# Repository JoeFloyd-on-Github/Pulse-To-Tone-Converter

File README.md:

# Pulse-to-Tone Converter (ATtiny85)

An internal **pulse-to-tone converter**. It sits inside a classic rotary
telephone and turns the dial's pulses (loop interruptions) into **DTMF
tones**, so the phone works on a modern tone-only line or VoIP adapter. It is
built around an **ATtiny85** on a small PCB, **BRD170127**.

> **Origin and credit.** The design comes from the open-source
> **[Pulse to Tone Converter](https://hackaday.io/project/28557-pulse-to-tone-converter)**
> by **LieBtrau** (Christoph Tack) on Hackaday.io and
> [GitHub](https://github.com/LieBtrau/pulse-dtmf-converter). This repository
> documents the kit built from it (rev R2), analyses it, and adds a
> redesigned board (rev V3).

## Board revisions

Each revision has its own parts list, firmware and build instructions. Use
the folder for the board you have.

| | **Rev R2**: the original kit board | **Rev V3**: the redesign |
|---|---|---|
| Folder | [`hardware_r2/`](hardware_r2/README.md) | [`hardware_v3/`](hardware_v3/README.md) |
| Board | LieBtrau's BRD170127/2 (EasyEDA): Gerbers, schematic, BOM, photos | KiCad 9, routed and DRC-clean, in the same outline with the jacks in the same places ([`hardware_v3/kicad`](hardware_v3/kicad/README.md)) |
| What's different | — | runs on loop currents down to about 1.5 mA (R2 needs about 6.5 mA); a PNP helper on each shunt regulator; no op-amp; optional CR1632 backup |
| Firmware source | upstream commit **`31ae4ba` (2019-07-06)**, Arduino IDE era ([`hardware_r2/firmware`](hardware_r2/firmware/README.md)) | upstream **`593e746` (2023)** plus V3 battery control ([`hardware_v3/firmware`](hardware_v3/firmware/README.md)) |
| Firmware image | `hardware_r2/firmware/images/ATTINY85V@SOIC8.hex` (production) | `hardware_v3/firmware/images/pulse-dtmf-converter-v3.hex` |
| Send delay after the last digit | 3 s | 1.2 s (configurable) |
| PB2 (ATtiny pin 7) | "mode" input, never wired on the board | coin-cell enable (BATT_EN) |
| Toolchain | Arduino IDE 1.8.13 + ATTinyCore 1.4.1 + Bounce2 2.55 | Arduino IDE 2 or arduino-cli + ATTinyCore 1.5.2 + Bounce2 2.71 |
| Fuses | L 0xFF, H 0xD5 (BOD 2.7 V), E 0xFF | the same |
| Programming | Arduino Uno as ISP, chip in a SOIC-8 ZIF adapter; or an XGecu programmer | the same Uno setup, in circuit with a SOIC-8 clip; or an XGecu programmer |
| Build docs | the toolchain guide + `KIT_build.doc` | [`hardware_v3/firmware/README.md`](hardware_v3/firmware/README.md) §3–5 + the KiCad fab files |
| Status | built and sold as a kit | designed and simulated; **not built yet** |

### About the firmware versions

Upstream's code changed after the R2 kits were made. The repo used to carry
upstream's **2023** source as if it were the kit firmware. It is not: the R2
production image was rebuilt from the **2019** source and matches it in size,
constants and RAM layout. The 2023 update moved the project from the Arduino
IDE to **PlatformIO**, shortened the send delay from 3 s to 1.2 s, and bounded
the digit buffer. The details are in
[`hardware_r2/firmware/README.md`](hardware_r2/firmware/README.md) §1 and §4.

## Also in this repo

| Path | Contents |
|---|---|
| [`ANALYSIS.md`](ANALYSIS.md) | engineering analysis of the original board and firmware: power, regulators, pulse decoding, DTMF generation, features |
| [`hardware_v3/spice`](hardware_v3/spice/README.md) | ngspice comparison of R2 and V3 |
| `third_party/` | **ATTinyCore** ([Spence Konde](https://github.com/SpenceKonde/ATTinyCore); a 1.4.2-dev snapshot; see its `LICENSE.md`) and **Bounce2** 2.55 ([Thomas Fredericks](https://github.com/thomasfredericks/Bounce2), MIT), as bundled with the R2 kit build |
| `WEB_SAVES/` | local copies of the upstream web pages and the ETSI DTMF specification, in case the sites go offline |

## License

- **Firmware:** both `hardware_r2/firmware` (upstream, verbatim) and
  `hardware_v3/firmware` (upstream plus the V3 changes) are **GPL v3**,
  © 2018 Christoph Tack. See the `LICENSE` file in each folder.
- **Bundled libraries** (ATTinyCore, Bounce2) keep their own licenses.
- The **documentation** (`ANALYSIS.md`, the READMEs, the SPICE and KiCad work)
  is this project's own. The boards derive from the upstream design; check the
  upstream project before redistributing hardware.

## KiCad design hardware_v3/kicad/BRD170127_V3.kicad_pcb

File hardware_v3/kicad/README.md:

# BRD170127 rev V3: KiCad design and manufacturing files

This is a routed, DRC-clean, 2-layer board in the rev-R2 outline (49 × 34 mm).
The three RJ11 jacks are in the same places as on R2, so V3 is a drop-in
replacement. The circuit is the one simulated in [`../spice`](../spice).

**Open in KiCad 9:** `BRD170127_V3.kicad_pro`. The project-local libraries are
`BRD170127.pretty` (the RJ11 footprint copied from the R2 board, and the
cell-lead pads) and `BRD170127.kicad_sym` (TLV431 with the onsemi SOT-23 pinout).

## Status

| Check | Result |
|---|---|
| DRC (`kicad-cli pcb drc --severity-all`) | **0 violations, 0 unconnected** |
| Schematic parity | **0 issues** |
| ERC | no electrical errors. The only warnings are that kicad-cli has no global symbol-library table on this machine; the symbols are embedded in the schematic. |
| R2 hole compatibility | all 18 jack pins and 6 locating posts match the R2 drill file to within 0.02 mm. C1 sits 0.3 mm higher, to clear the rotary jack's body. |

## Ordering (`fab/`)

| File | Use |
|---|---|
| `BRD170127_V3_gerbers.zip` | upload to the PCB fab: 2 layers, 1.6 mm, HASL or ENIG, any colour |
| `BRD170127_V3_bom_jlc.csv`, `BRD170127_V3_cpl_jlc.csv` | JLCPCB-style assembly files for the 41 top-side SMD parts |
| `BRD170127_V3_bom.csv` | the full BOM, including the hand-soldered parts |
| `BRD170127_V3_schematic.pdf` | the schematic |
| `BRD170127_V3_assembly.pdf` | every reference designator. 14 labels did not fit on the silkscreen of this dense board and appear only here. |
| `render_top.png`, `render_bottom.png` | 3-D renders |

Design rules: tracks at least 0.2 mm (0.5 mm on the line, VCC, VEE and GND
nets), clearance 0.2 mm, vias 0.6/0.3 mm (0.8/0.4 mm on line nets), GND pour
on both layers. Any standard 2-layer service can make it.

**Before you order:**
- **Fill in the LCSC numbers.** They are known for the parts reused from R2:
  BAT46WH C127989, TLV431A C56765, BC856B C181144, ATtiny85V C152192 and the
  8 MHz crystal C108703. The 0805 passives, BCX53-16 (Q2/Q4) and DMG2301L (Q3)
  have only an MPN or value. Pick stock parts at order time.
- In the fab's assembly preview, check the rotation of the SOT-23/SOT-89/SOIC
  parts. KiCad and JLCPCB sometimes disagree on the zero orientation.
- **Hand-soldered parts:** the three RJ11 jacks (mounted as on R2), the
  470 µF / 6.3 V radial C1 (8 mm diameter, 3.5 mm pitch), and the CR1632 holder
  on flying leads to the BT1 pads (+ is the square pad).

## Circuit changes from the original (rev R2)

| Area | Original | V3 | Why |
|---|---|---|---|
| Upper shunt | TLV431 alone, 4.59 V, plus a 1k bleeder | TLV431 U2 + BCX53 Q2 (R15 470, R16 220, C12 1n), 5.0 V (R1 100k / R6 33k), 22k bleeder R17 | each TLV431 only biases its PNP; R17 still pulls VCC down quickly so pulse breaks are detected |
| Lower shunt / line modulator | TLV431 U3 carries the whole loop current | U3 + BCX53 Q4 (R19 470, R20 220), R5 47k | the original runs U3 at 25–40 mA against a 15 mA rating |
| DTMF filter | MCP6022: 4th-order active filter + V-to-I | passive 2-pole RC (R12/R13/C8, R10/C9) into Q1 (R2 39k emitter resistor) | removes 2 mA of standing current |
| Reservoir | 470 µF behind D5 | same | the simulation shows it rides through dialing down to about 1.5 mA of loop current |
| Coin cell | none | CR1632 → Q3 (DMG2301L) → D6 → VDD; gate pull-up R18 1M; BATT_EN = **PB2 (pin 7)** | kept at the owner's request; the simulation shows it is rarely needed |
| Test points | none | TP1 VCC, TP2 VDD, TP3 BATT+, TP4 BATT_EN, TP5 CELL, TP6 GND | for bench verification (see `../spice/README.md`) |
| Passive parts | 1206 | 0805 | the extra parts have to fit the same area |

**Firmware:** BATT_EN is on **PB2**, the only free pin: PB1 is the DTMF PWM
output (OC1A), and the crystal uses PB3/PB4. The V3 firmware, its tools and
fuses, and the in-circuit programming (Arduino as ISP with a SOIC-8 clip on U1)
are in [`../firmware`](../firmware/README.md).

## Regenerating

Everything is built from `design.py`, which defines the parts, nets and
placement:

```sh
python3 gen_sch.py          # schematic (net-label style; symbols flattened and embedded)
python3 gen_pcb.py          # placed, unrouted board + project/library tables
python3 route.py            # import route/board.ses, widen neck-downs, refill pours, place labels
python3 make_fab.py         # DRC + parity + ERC, then everything in fab/
```

To route from scratch instead of reusing `route/board.ses`:

```sh
FREEROUTING_JAR=/path/to/freerouting-2.5.0.jar python3 route.py --autoroute
```

Freerouting is run headless with analytics disabled and Java's network access
pointed at a dead proxy.

If you edit the board by hand in KiCad, stop using the generators: they
overwrite the `.kicad_pcb` and `.kicad_sch` files.

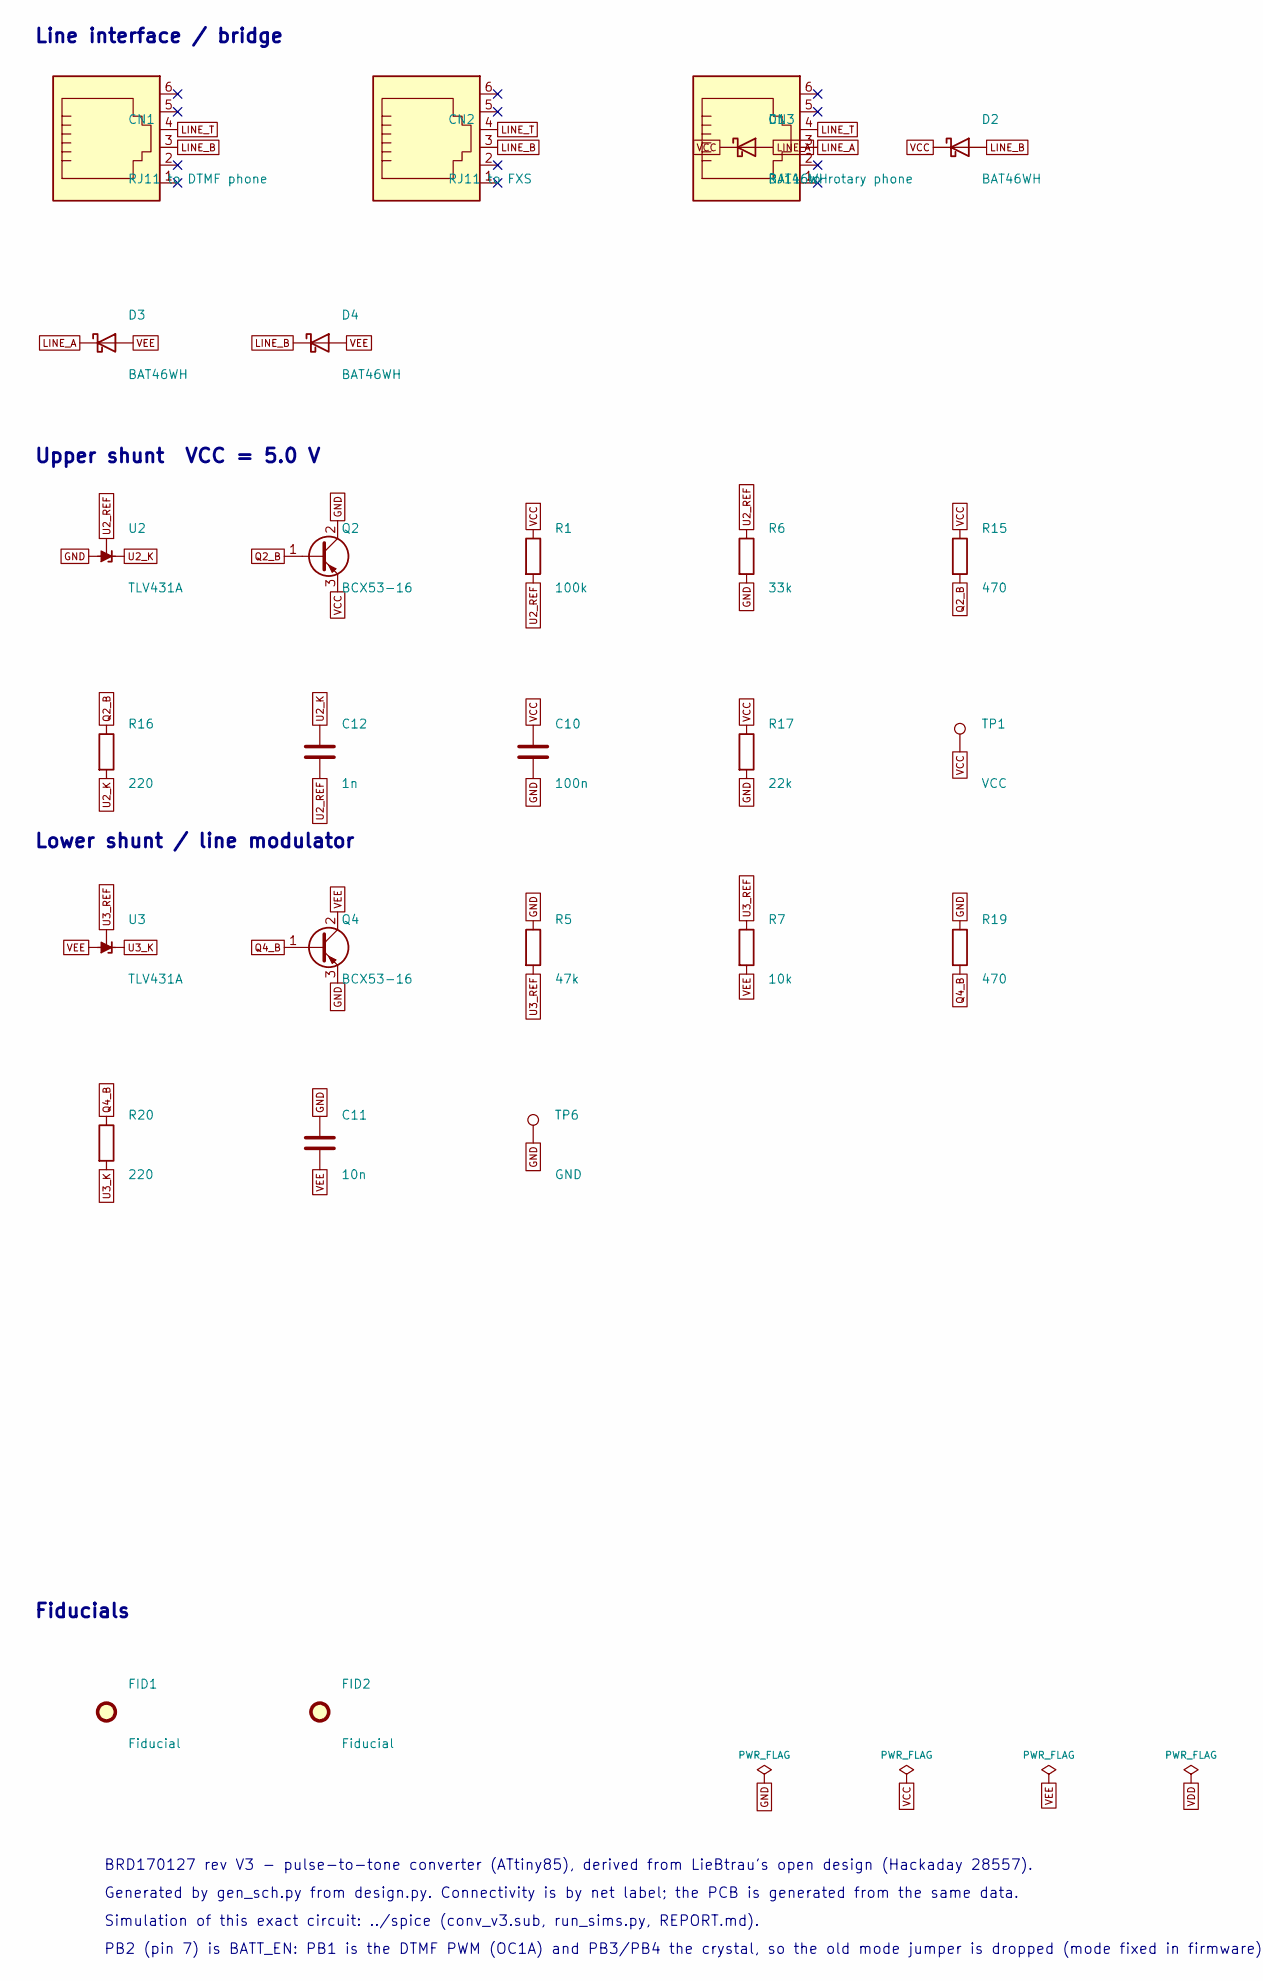
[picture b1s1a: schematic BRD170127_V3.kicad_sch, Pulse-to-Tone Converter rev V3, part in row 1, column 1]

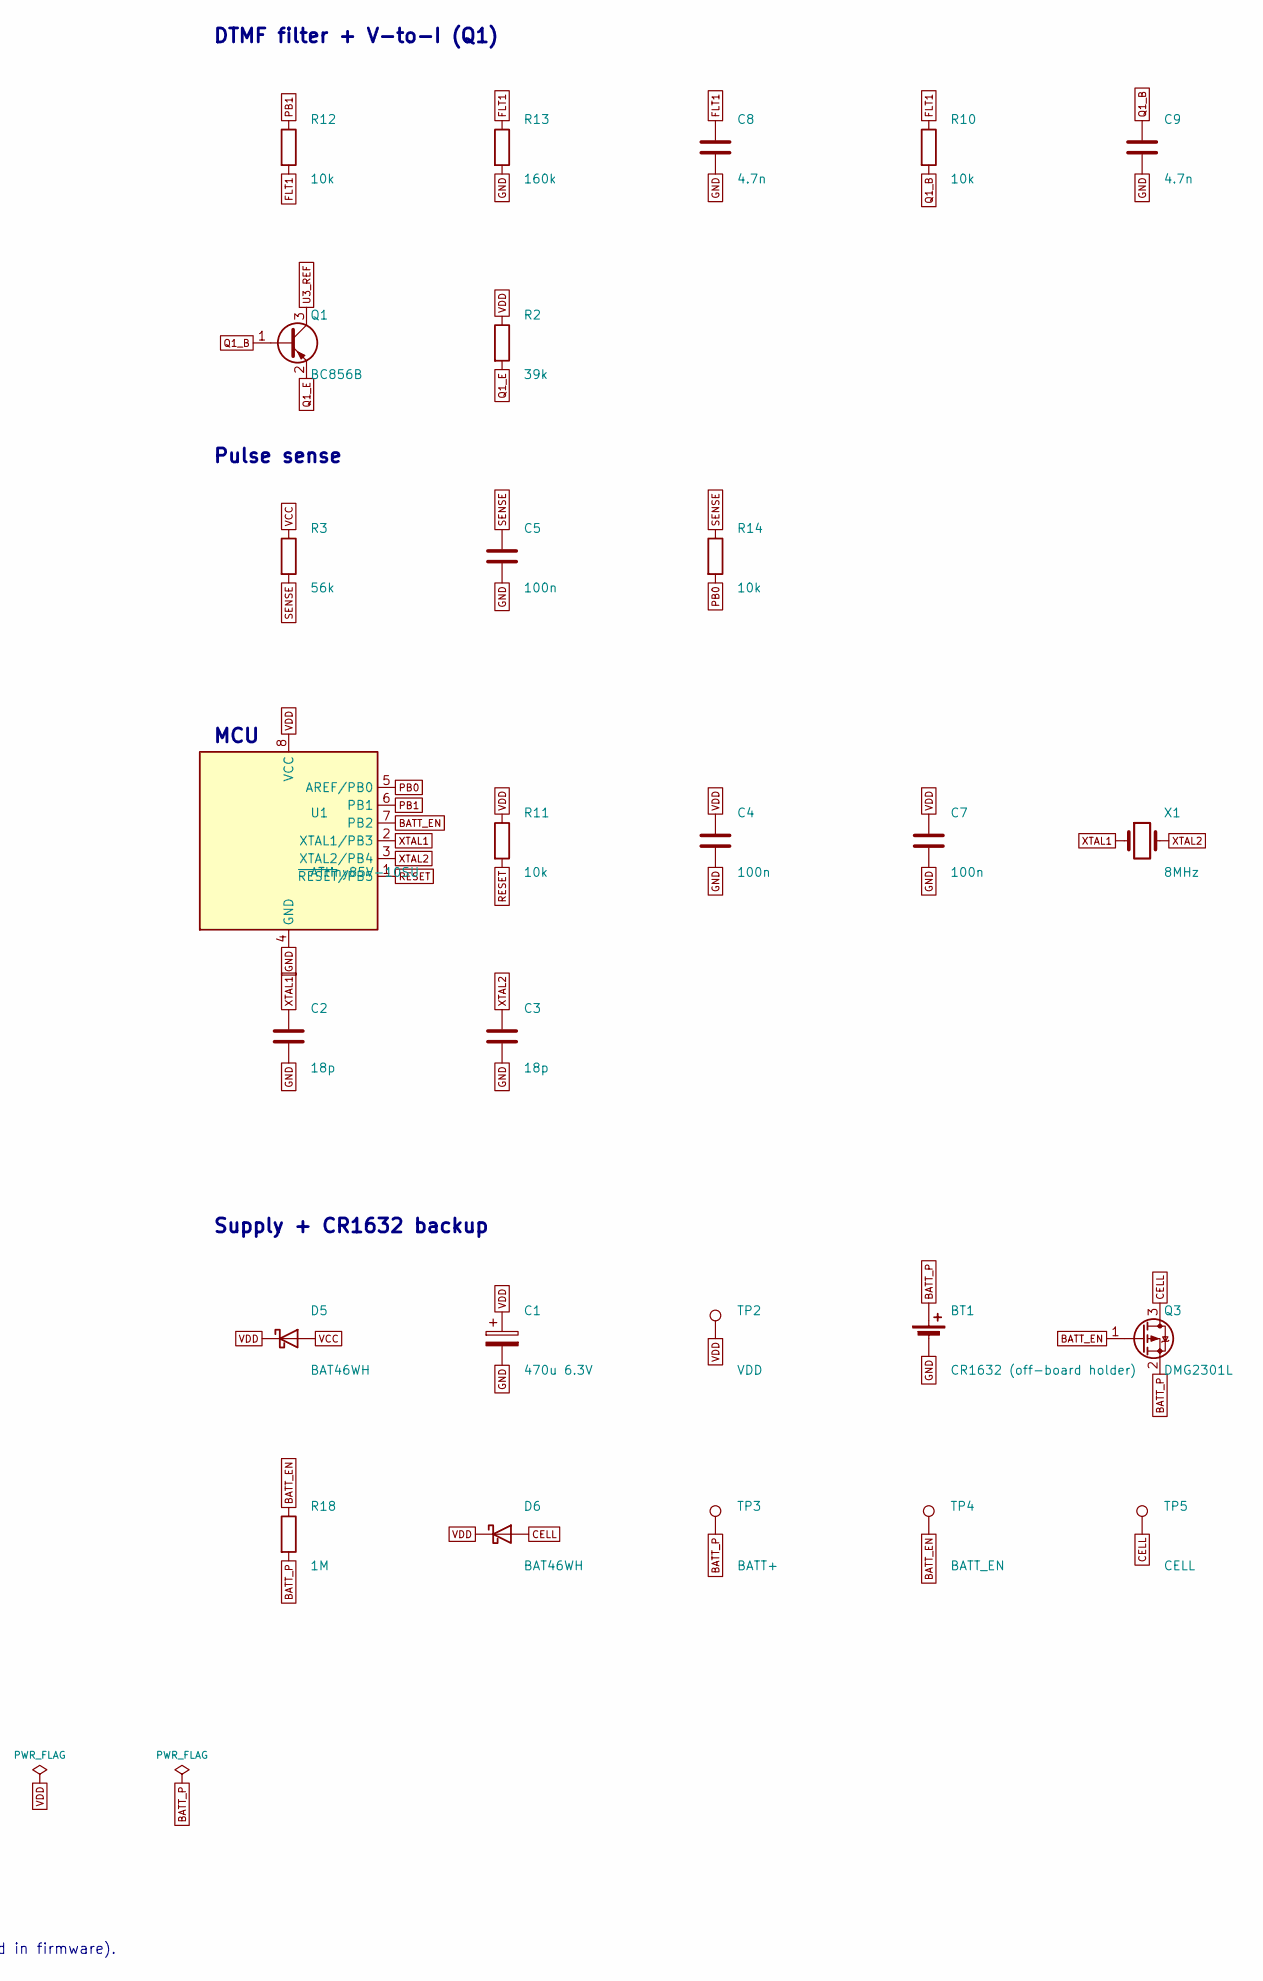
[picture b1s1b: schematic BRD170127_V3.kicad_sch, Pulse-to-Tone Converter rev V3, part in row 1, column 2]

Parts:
BT1: CR1632 (off-board holder); CELL_LEADS_2PAD; MPN CR1632 + wire-lead holder
C1: 470u 6.3V; CP_Radial_D8.0mm_P3.50mm; MPN 470uF 6.3V radial 8 mm, 3.5 mm pitch
C2, C3: 18p; C_0805_2012Metric
C4, C5, C7, C10: 100n; C_0805_2012Metric
C8, C9: 4.7n; C_0805_2012Metric
C11: 10n; C_0805_2012Metric
C12: 1n; C_0805_2012Metric
CN1: RJ11 to DTMF phone; RJ11_6P6C_BRD170127; MPN 6P6C side-entry, as rev R2
CN2: RJ11 to FXS; RJ11_6P6C_BRD170127; MPN 6P6C side-entry, as rev R2
CN3: RJ11 to rotary phone; RJ11_6P6C_BRD170127; MPN 6P6C side-entry, as rev R2
D1, D2, D3, D4, D5, D6: BAT46WH; D_SOD-123; MPN BAT46WH; LCSC C127989
FID1, FID2: Fiducial; Fiducial_1mm_Mask2mm
Q1: BC856B; SOT-23; MPN BC856B; LCSC C181144
Q2, Q4: BCX53-16; SOT-89-3; MPN BCX53-16
Q3: DMG2301L; SOT-23; MPN DMG2301L-7
R1: 100k; R_0805_2012Metric
R2: 39k; R_0805_2012Metric
R3: 56k; R_0805_2012Metric
R5: 47k; R_0805_2012Metric
R6: 33k; R_0805_2012Metric
R7, R10, R11, R12, R14: 10k; R_0805_2012Metric
R13: 160k; R_0805_2012Metric
R15, R19: 470; R_0805_2012Metric
R16, R20: 220; R_0805_2012Metric
R17: 22k; R_0805_2012Metric
R18: 1M; R_0805_2012Metric
TP1: VCC; TestPoint_Pad_D1.5mm
TP2: VDD; TestPoint_Pad_D1.5mm
TP3: BATT+; TestPoint_Pad_D1.5mm
TP4: BATT_EN; TestPoint_Pad_D1.5mm
TP5: CELL; TestPoint_Pad_D1.5mm
TP6: GND; TestPoint_Pad_D1.5mm
U1: ATtiny85V-10SU; SOIC-8_5.3x5.3mm_P1.27mm; MPN ATTINY85V-10SU; LCSC C152192
U2, U3: TLV431A; SOT-23; MPN TLV431ASN1T1G; LCSC C56765
X1: 8MHz; Crystal_SMD_HC49-SD; MPN HC-49/US SMD 8.000 MHz 18 pF; LCSC C108703

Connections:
BATT_EN: Q3.1 (G), R18.1, TP4.1, U1.7 (PB2)
BATT_P: BT1.1 (+), Q3.2 (S), R18.2, TP3.1
CELL: D6.2 (A), Q3.3 (D), TP5.1
FLT1: C8.1, R10.1, R12.2, R13.1
GND: BT1.2 (-), C1.2, C2.2, C3.2, C4.2, C5.2, C7.2, C8.2, C9.2, C10.2, C11.1, Q2.2 (C), Q4.3 (E), R5.1, R6.2, R13.2, R17.2, R19.1, TP6.1, U1.4 (GND), U2.3 (A)
LINE_A: CN3.3, D1.2 (A), D3.1 (K)
LINE_B: CN1.3, CN2.3, D2.2 (A), D4.1 (K)
LINE_T: CN1.4, CN2.4, CN3.4
PB0: R14.2, U1.5 (AREF/PB0)
PB1: R12.1, U1.6 (PB1)
Q1_B: C9.1, Q1.1 (B), R10.2
Q1_E: Q1.2 (E), R2.2
Q2_B: Q2.1 (B), R15.2, R16.1
Q4_B: Q4.1 (B), R19.2, R20.1
RESET: R11.2, U1.1 (~RESET/PB5)
SENSE: C5.1, R3.2, R14.1
U2_K: C12.1, R16.2, U2.2 (K)
U2_REF: C12.2, R1.2, R6.1, U2.1 (REF)
U3_K: R20.2, U3.2 (K)
U3_REF: Q1.3 (C), R5.2, R7.1, U3.1 (REF)
VCC: C10.1, D1.1 (K), D2.1 (K), D5.2 (A), Q2.3 (E), R1.1, R3.1, R15.1, R17.1, TP1.1
VDD: C1.1, C4.1, C7.1, D5.1 (K), D6.1 (K), R2.1, R11.1, TP2.1, U1.8 (VCC)
VEE: C11.2, D3.2 (A), D4.2 (A), Q4.2 (C), R7.2, U3.3 (A)
XTAL1: C2.1, U1.2 (XTAL1/PB3), X1.1
XTAL2: C3.1, U1.3 (XTAL2/PB4), X1.2

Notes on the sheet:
Line interface / bridge
Upper shunt VCC = 5.0 V
Lower shunt / line modulator
DTMF filter + V-to-I (Q1)
Pulse sense
MCU
Supply + CR1632 backup
Fiducials
BRD170127 rev V3 - pulse-to-tone converter (ATtiny85), derived from LieBtrau's open design (Hackaday 28557).
Generated by gen_sch.py from design.py. Connectivity is by net label; the PCB is generated from the same data.
Simulation of this exact circuit: ../spice (conv_v3.sub, run_sims.py, REPORT.md).
PB2 (pin 7) is BATT_EN: PB1 is the DTMF PWM (OC1A) and PB3/PB4 the crystal, so the old mode jumper is dropped (mode fixed in firmware).

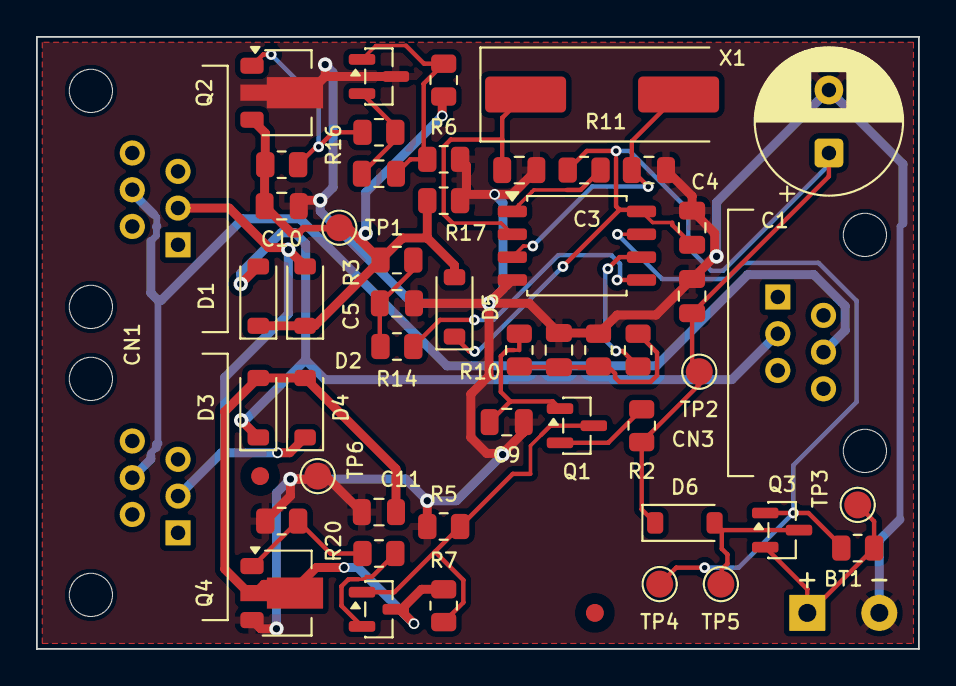
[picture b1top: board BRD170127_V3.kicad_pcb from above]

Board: 2 copper layers, 49.0 x 34.0 mm, 54 parts (0 on the bottom side), 25 nets.

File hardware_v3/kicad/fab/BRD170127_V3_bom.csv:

Qty,Value,Designators,Footprint,MPN / description,LCSC
1,CR1632 (off-board holder),BT1,CELL_LEADS_2PAD,CR1632 + wire-lead holder,
1,470u 6.3V,C1,CP_Radial_D8.0mm_P3.50mm,"470uF 6.3V radial 8 mm, 3.5 mm pitch",
2,18p,C2 C3,C_0805_2012Metric,,
4,100n,C4 C5 C7 C10,C_0805_2012Metric,,
2,4.7n,C8 C9,C_0805_2012Metric,,
1,10n,C11,C_0805_2012Metric,,
1,1n,C12,C_0805_2012Metric,,
1,RJ11 to DTMF phone,CN1,RJ11_6P6C_BRD170127,"6P6C side-entry, as rev R2",
1,RJ11 to FXS,CN2,RJ11_6P6C_BRD170127,"6P6C side-entry, as rev R2",
1,RJ11 to rotary phone,CN3,RJ11_6P6C_BRD170127,"6P6C side-entry, as rev R2",
6,BAT46WH,D1 D2 D3 D4 D5 D6,D_SOD-123,BAT46WH,C127989
1,BC856B,Q1,SOT-23,BC856B,C181144
2,BCX53-16,Q2 Q4,SOT-89-3,BCX53-16,
1,DMG2301L,Q3,SOT-23,DMG2301L-7,
1,100k,R1,R_0805_2012Metric,,
1,39k,R2,R_0805_2012Metric,,
1,56k,R3,R_0805_2012Metric,,
1,47k,R5,R_0805_2012Metric,,
1,33k,R6,R_0805_2012Metric,,
5,10k,R7 R10 R11 R12 R14,R_0805_2012Metric,,
1,160k,R13,R_0805_2012Metric,,
2,470,R15 R19,R_0805_2012Metric,,
2,220,R16 R20,R_0805_2012Metric,,
1,22k,R17,R_0805_2012Metric,,
1,1M,R18,R_0805_2012Metric,,
1,ATtiny85V-10SU,U1,SOIC-8_5.3x5.3mm_P1.27mm,ATTINY85V-10SU,C152192
2,TLV431A,U2 U3,SOT-23,TLV431ASN1T1G,C56765
1,8MHz,X1,Crystal_SMD_HC49-SD,HC-49/US SMD 8.000 MHz 18 pF,C108703

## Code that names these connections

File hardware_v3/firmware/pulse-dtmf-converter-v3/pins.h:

#pragma once

#include "Arduino.h"

// ATtiny85 pin map for BRD170127 rev V3 (see ../README.md).
//   pin 1  PB5  RESET (R11 10k pull-up)
//   pin 2  PB3  crystal X1 (8 MHz)
//   pin 3  PB4  crystal X1
//   pin 5  PB0  loop/pulse sense (VCC -> R3/C5 -> R14): LOW = loop open
//   pin 6  PB1  DTMF PWM output OC1A (hard-coded in dtmfgenerator.cpp)
//   pin 7  PB2  BATT_EN: LOW = coin cell connected; input (high-Z) = cell off
//               (R18 1M pulls Q3's gate to BATT+). On the R2 board this was the
//               unused "mode select" input.
const int PIN_LOOP_SENSE = 0;   // upstream name: PIN_DTMF_OUT (it was always the pulse input)
const int PIN_BATT_EN    = 2;   // upstream: PIN_MODE_SELECT

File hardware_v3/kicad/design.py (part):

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    "Q1": ("BC856B", SOT23, "Transistor_BJT:BC856", "BC856B", "C181144",
           {"1": "Q1_B", "2": "Q1_E", "3": "U3_REF"}, (30.6, 11.0, 0)),
    "R2": ("39k", R, "Device:R", "", "", {"1": "VDD", "2": "Q1_E"}, (34.0, 11.0, 90)),
    "R12": ("10k", R, "Device:R", "", "", {"1": "PB1", "2": "FLT1"}, (34.0, 17.2, 90)),
    "R13": ("160k", R, "Device:R", "", "", {"1": "FLT1", "2": "GND"}, (36.2, 14.6, 90)),
    "C8": ("4.7n", C, "Device:C", "", "", {"1": "FLT1", "2": "GND"}, (31.8, 17.2, 90)),
    "R10": ("10k", R, "Device:R", "", "", {"1": "FLT1", "2": "Q1_B"}, (29.6, 17.2, 90)),
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    # ---------------------------------------------------------- pulse sense
    "R3": ("56k", R, "Device:R", "", "", {"1": "VCC", "2": "SENSE"}, (22.0, 20.0, 0)),
    "C5": ("100n", C, "Device:C", "", "", {"1": "SENSE", "2": "GND"}, (22.0, 17.8, 0)),
    "R14": ("10k", R, "Device:R", "", "", {"1": "SENSE", "2": "PB0"}, (25.8, 17.8, 0)),
    # ------------------------------------------------------------------- MCU
    "U1": ("ATtiny85V-10SU", "Package_SO:SOIC-8_5.3x5.3mm_P1.27mm", "MCU_Microchip_ATtiny:ATtiny85V-10S",
           "ATTINY85V-10SU", "C152192",
           {"1": "RESET", "2": "XTAL1", "3": "XTAL2", "4": "GND", "5": "PB0", "6": "PB1",
            "7": "BATT_EN", "8": "VDD"}, (31.0, 23.0, 0)),
    "R11": ("10k", R, "Device:R", "", "", {"1": "VDD", "2": "RESET"}, (36.8, 21.0, 90)),
    "C4": ("100n", C, "Device:C", "", "", {"1": "VDD", "2": "GND"}, (35.2, 26.4, 0)),
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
